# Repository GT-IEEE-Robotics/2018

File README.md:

# 2018
- 2018 Georgia Tech IEEE Hardware Team Repository
- Competition: 2018 Southeastcon Robotics Competition in Jacksonville, Florida
- Objective: to create an autonomous robot to navigate through various tasks in a minimal time frame

### Contents
- `Application`
    - Graphic User Interface robot controller
- `Competiton`
    - Final competition code and documentation
- `Distance Sensing`
    - Course detection and localization
- `Load Lifting`
    - Resources for lifting treasure weight
- `Miscellaneous`
    - Non competition relevant resouces
- `Motor Controller`
    - Motor control code and interface API
- `Navigation`
    - Course navigation theory and controller
- `Photodiode`
    - Start up infared signal generation and detection 
- `PRU`
    - Beaglebone black programmable real time units quadrature encoder reading
- [Rules](USF_IEEE_2018_SoutheastCon_HardwareRules_V3_2.pdf)

### To Do's
- [ ] List TODO's

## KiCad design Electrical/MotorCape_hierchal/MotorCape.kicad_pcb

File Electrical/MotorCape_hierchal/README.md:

# Arduino KiCad Library
Library of schematic components and footprints of common Arduino boards for KiCAD.

Currently included are:
- Arduino 101 Shield
- Arduino Due Shield
- Arduino Leonard Shied
- Arduino Mega 2560 Shield
- Arduino Micro Socket
- Arduino Uno Shield
- Arduino Zero Shield

Shield means the Arduino is designed to plug in from beneath your PCB; socket means it is designed to plug in from above.

## Library Setup
To add this library to your KiCad Project, do the following steps:
1. Copy the source files to your Project. Make sure that the Arduino.pretty folder structure is preserved.
2. In EeSchema (the schematic editor of KiCad) go to Preferences -> Component Libraries. Click the "Add" button next to "Component library files".
3. Navigate to your project folder, select "arduino.lib" and click "open".
4. You may wish to adjust the newly added arduino schematic library to be near the top of the load order using the "Up" and "Down" buttons, but this is optional and is only relevant if you have other libraries that use the same names for parts.
5. OK out and exit EeSchema. Open PcbNew (the PCB editor of KiCad) go to Preferences -> Footprint Libraries Manager.
6. Select the "Project Specific Libraries" tab and then click "Append Library".
7. In the new line of the table, set Library Path to "$(KIPRJMOD)\Arduino.pretty" and ensure Plugin Type is "KiCad". Options and Description can be left blank. You should set Nickname to something descriptive - like "Arduino" for example!
8. All done: you are now ready to use these schematic components and footprints!

## Comments, Requests, Bugs & Contributions
All are welcome. Please file an "Issue" in the Bug Tracker.

## License
This library is licensed under the GNU LGPL v2.1, which can be found in file LICENSE.txt.

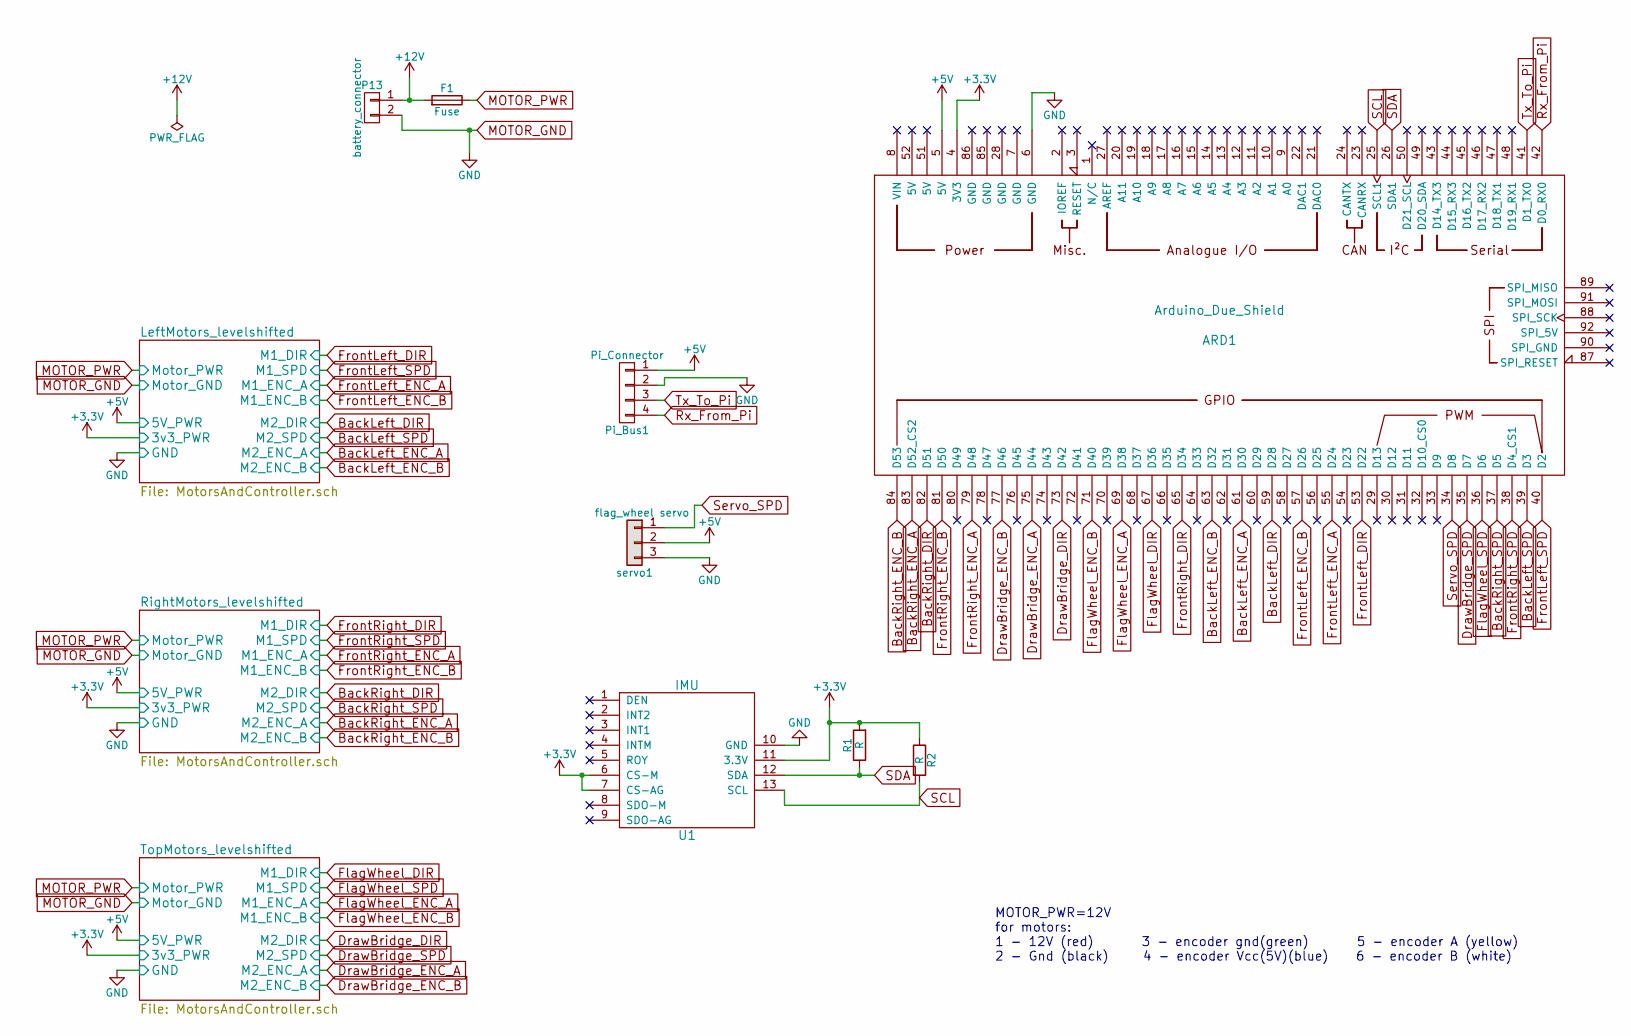
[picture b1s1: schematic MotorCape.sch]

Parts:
ARD1: Arduino_Due_Shield
F1: Fuse; Fuseholder_horizontal_inline_1_25x0_25_inch
P13: battery_connector; Molex_Sabre_43160-XX02_02x7.49mm_Vertical_BoardLock
Pi_Bus1: Pi_Connector; Pin_Header_Latched_1x04
R1, R2: R; R_Axial_DIN0204_L3.6mm_D1.6mm_P5.08mm_Horizontal
U1: IMU
servo1: flag_wheel servo; Pin_Header_Latched_1x03

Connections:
+3V3: ARD1.4 (3V3), R1.2, R2.1, U1.6 (CS-M), U1.7 (CS-AG), U1.11 (3.3V); also elsewhere on the board
+5V: ARD1.5 (5V), Pi_Bus1.1, servo1.2; also elsewhere on the board
+12V: F1.2, P13.1
BackLeft_DIR: ARD1.59 (D28); also elsewhere on the board
BackLeft_ENC_A: ARD1.61 (D30); also elsewhere on the board
BackLeft_ENC_B: ARD1.63 (D32); also elsewhere on the board
BackLeft_SPD: ARD1.39 (D3); also elsewhere on the board
BackRight_DIR: ARD1.82 (D51); also elsewhere on the board
BackRight_ENC_A: ARD1.83 (D52_CS2); also elsewhere on the board
BackRight_ENC_B: ARD1.84 (D53); also elsewhere on the board
BackRight_SPD: ARD1.37 (D5); also elsewhere on the board
DrawBridge_DIR: ARD1.73 (D42); also elsewhere on the board
DrawBridge_ENC_A: ARD1.75 (D44); also elsewhere on the board
DrawBridge_ENC_B: ARD1.77 (D46); also elsewhere on the board
DrawBridge_SPD: ARD1.35 (D7); also elsewhere on the board
FlagWheel_DIR: ARD1.67 (D36); also elsewhere on the board
FlagWheel_ENC_A: ARD1.69 (D38); also elsewhere on the board
FlagWheel_ENC_B: ARD1.71 (D40); also elsewhere on the board
FlagWheel_SPD: ARD1.36 (D6); also elsewhere on the board
FrontLeft_DIR: ARD1.53 (D22); also elsewhere on the board
FrontLeft_ENC_A: ARD1.55 (D24); also elsewhere on the board
FrontLeft_ENC_B: ARD1.57 (D26); also elsewhere on the board
FrontLeft_SPD: ARD1.40 (D2); also elsewhere on the board
FrontRight_DIR: ARD1.65 (D34); also elsewhere on the board
FrontRight_ENC_A: ARD1.79 (D48); also elsewhere on the board
FrontRight_ENC_B: ARD1.81 (D50); also elsewhere on the board
FrontRight_SPD: ARD1.38 (D4_CS1); also elsewhere on the board
MOTOR_GND: ARD1.6 (GND), P13.2, Pi_Bus1.2, U1.10 (GND), servo1.3; also elsewhere on the board
MOTOR_PWR: F1.1; also elsewhere on the board
Rx_From_Pi: ARD1.42 (D0_RX0), Pi_Bus1.4
SCL: ARD1.25 (SCL1), R2.2, U1.13 (SCL)
SDA: ARD1.26 (SDA1), R1.1, U1.12 (SDA)
Servo_SPD: ARD1.34 (D8), servo1.1
Tx_To_Pi: ARD1.41 (D1_TX0), Pi_Bus1.3

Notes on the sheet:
MOTOR_PWR=12V for motors: 1 - 12V (red) 3 - encoder gnd(green) 5 - encoder A (yellow) 2 - Gnd (black) 4 - encoder Vcc(5V)(blue) 6 - encoder B (white)

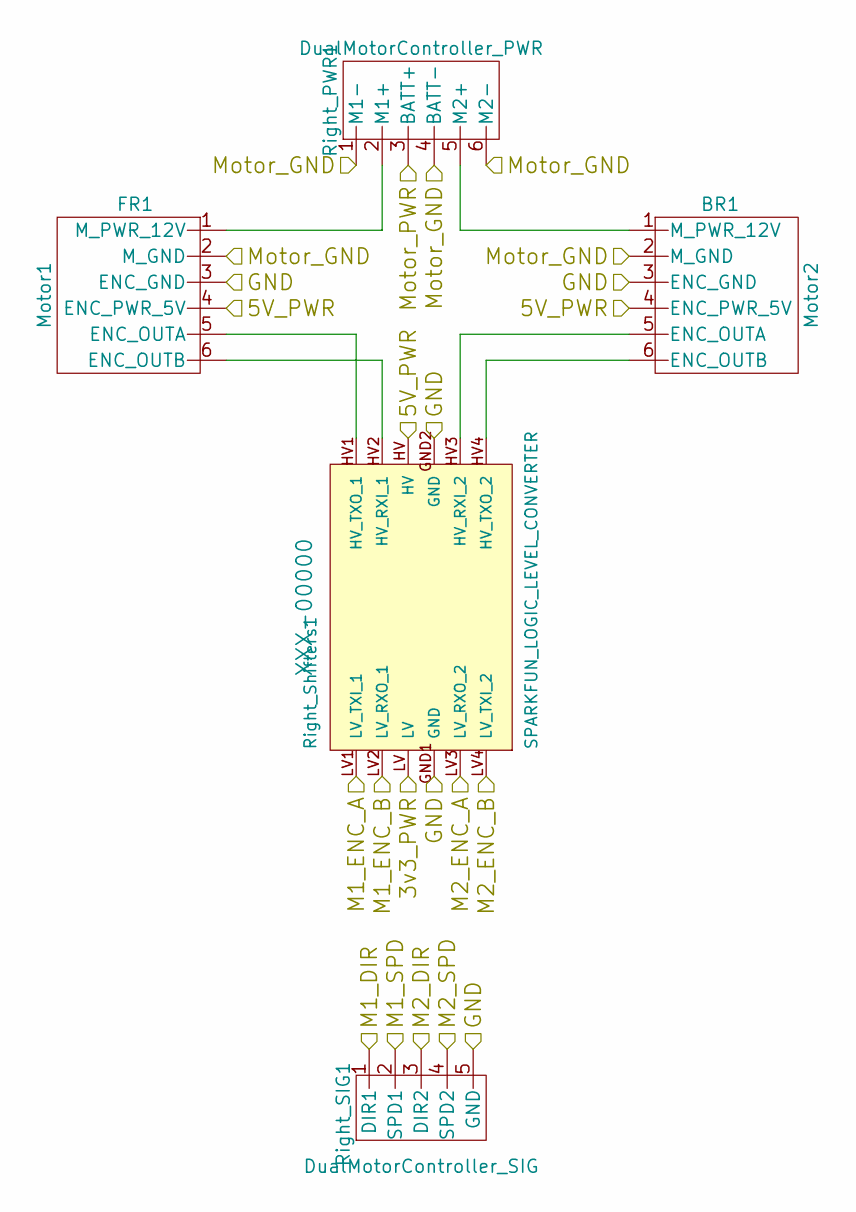
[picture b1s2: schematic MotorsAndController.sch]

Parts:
BL1: Motor2; Pin_Header_Latched_1x06
FL1: Motor1; Pin_Header_Latched_1x06
Left_PWR1: DualMotorController_PWR; PhoenixContact_MSTBA-G_06x5.08mm_Angled
Left_SIG1: DualMotorController_SIG; Pin_Header_Latched_1x05
Left_Shifters1: SPARKFUN_LOGIC_LEVEL_CONVERTER

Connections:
+3V3: Left_Shifters1.LV; also elsewhere on the board
+5V: BL1.4 (ENC_PWR_5V), FL1.4 (ENC_PWR_5V), Left_Shifters1.HV; also elsewhere on the board
BackLeft_DIR: Left_SIG1.3 (DIR2); also elsewhere on the board
BackLeft_ENC_A: Left_Shifters1.LV3 (LV_RXO_2); also elsewhere on the board
BackLeft_ENC_B: Left_Shifters1.LV4 (LV_TXI_2); also elsewhere on the board
BackLeft_SPD: Left_SIG1.4 (SPD2); also elsewhere on the board
FrontLeft_DIR: Left_SIG1.1 (DIR1); also elsewhere on the board
FrontLeft_ENC_A: Left_Shifters1.LV1 (LV_TXI_1); also elsewhere on the board
FrontLeft_ENC_B: Left_Shifters1.LV2 (LV_RXO_1); also elsewhere on the board
FrontLeft_SPD: Left_SIG1.2 (SPD1); also elsewhere on the board
MOTOR_GND: BL1.2 (M_GND), BL1.3 (ENC_GND), FL1.2 (M_GND), FL1.3 (ENC_GND), Left_PWR1.1 (M1-), Left_PWR1.4 (BATT-), Left_PWR1.6 (M2-), Left_SIG1.5 (GND), Left_Shifters1.GND1 (GND), Left_Shifters1.GND2 (GND); also elsewhere on the board
MOTOR_PWR: Left_PWR1.3 (BATT+); also elsewhere on the board
unnamed: BL1.1 (M_PWR_12V), Left_PWR1.5 (M2+)
unnamed: BL1.5 (ENC_OUTA), Left_Shifters1.HV3 (HV_RXI_2)
unnamed: BL1.6 (ENC_OUTB), Left_Shifters1.HV4 (HV_TXO_2)
unnamed: FL1.1 (M_PWR_12V), Left_PWR1.2 (M1+)
unnamed: FL1.5 (ENC_OUTA), Left_Shifters1.HV1 (HV_TXO_1)
unnamed: FL1.6 (ENC_OUTB), Left_Shifters1.HV2 (HV_RXI_1)

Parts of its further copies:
BR1: Motor2; Pin_Header_Latched_1x06
DrawBridge1: Motor2; Pin_Header_Latched_1x06
FR1: Motor1; Pin_Header_Latched_1x06
FlagWheel1: Motor1; Pin_Header_Latched_1x06
Right_PWR1: DualMotorController_PWR; PhoenixContact_MSTBA-G_06x5.08mm_Angled
Right_SIG1: DualMotorController_SIG; Pin_Header_Latched_1x05
Right_Shifters1: SPARKFUN_LOGIC_LEVEL_CONVERTER
Top_PWR1: DualMotorController_PWR; PhoenixContact_MSTBA-G_06x5.08mm_Angled
Top_SIG1: DualMotorController_SIG; Pin_Header_Latched_1x05
Top_Shifters1: SPARKFUN_LOGIC_LEVEL_CONVERTER

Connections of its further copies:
+3V3: Right_Shifters1.LV, Top_Shifters1.LV; also elsewhere on the board
+5V: BR1.4 (ENC_PWR_5V), DrawBridge1.4 (ENC_PWR_5V), FR1.4 (ENC_PWR_5V), FlagWheel1.4 (ENC_PWR_5V), Right_Shifters1.HV, Top_Shifters1.HV; also elsewhere on the board
BackRight_DIR: Right_SIG1.3 (DIR2); also elsewhere on the board
BackRight_ENC_A: Right_Shifters1.LV3 (LV_RXO_2); also elsewhere on the board
BackRight_ENC_B: Right_Shifters1.LV4 (LV_TXI_2); also elsewhere on the board
BackRight_SPD: Right_SIG1.4 (SPD2); also elsewhere on the board
DrawBridge_DIR: Top_SIG1.3 (DIR2); also elsewhere on the board
DrawBridge_ENC_A: Top_Shifters1.LV3 (LV_RXO_2); also elsewhere on the board
DrawBridge_ENC_B: Top_Shifters1.LV4 (LV_TXI_2); also elsewhere on the board
DrawBridge_SPD: Top_SIG1.4 (SPD2); also elsewhere on the board
FlagWheel_DIR: Top_SIG1.1 (DIR1); also elsewhere on the board
FlagWheel_ENC_A: Top_Shifters1.LV1 (LV_TXI_1); also elsewhere on the board
FlagWheel_ENC_B: Top_Shifters1.LV2 (LV_RXO_1); also elsewhere on the board
FlagWheel_SPD: Top_SIG1.2 (SPD1); also elsewhere on the board
FrontRight_DIR: Right_SIG1.1 (DIR1); also elsewhere on the board
FrontRight_ENC_A: Right_Shifters1.LV1 (LV_TXI_1); also elsewhere on the board
FrontRight_ENC_B: Right_Shifters1.LV2 (LV_RXO_1); also elsewhere on the board
FrontRight_SPD: Right_SIG1.2 (SPD1); also elsewhere on the board
MOTOR_GND: BR1.2 (M_GND), BR1.3 (ENC_GND), DrawBridge1.2 (M_GND), DrawBridge1.3 (ENC_GND), FR1.2 (M_GND), FR1.3 (ENC_GND), FlagWheel1.2 (M_GND), FlagWheel1.3 (ENC_GND), Right_PWR1.1 (M1-), Right_PWR1.4 (BATT-), Right_PWR1.6 (M2-), Right_SIG1.5 (GND), Right_Shifters1.GND1 (GND), Right_Shifters1.GND2 (GND), Top_PWR1.1 (M1-), Top_PWR1.4 (BATT-), Top_PWR1.6 (M2-), Top_SIG1.5 (GND), Top_Shifters1.GND1 (GND), Top_Shifters1.GND2 (GND); also elsewhere on the board
MOTOR_PWR: Right_PWR1.3 (BATT+), Top_PWR1.3 (BATT+); also elsewhere on the board
unnamed: BR1.1 (M_PWR_12V), Right_PWR1.5 (M2+)
unnamed: BR1.5 (ENC_OUTA), Right_Shifters1.HV3 (HV_RXI_2)
unnamed: BR1.6 (ENC_OUTB), Right_Shifters1.HV4 (HV_TXO_2)
unnamed: DrawBridge1.1 (M_PWR_12V), Top_PWR1.5 (M2+)
unnamed: DrawBridge1.5 (ENC_OUTA), Top_Shifters1.HV3 (HV_RXI_2)
unnamed: DrawBridge1.6 (ENC_OUTB), Top_Shifters1.HV4 (HV_TXO_2)
unnamed: FR1.1 (M_PWR_12V), Right_PWR1.2 (M1+)
unnamed: FR1.5 (ENC_OUTA), Right_Shifters1.HV1 (HV_TXO_1)
unnamed: FR1.6 (ENC_OUTB), Right_Shifters1.HV2 (HV_RXI_1)
unnamed: FlagWheel1.1 (M_PWR_12V), Top_PWR1.2 (M1+)
unnamed: FlagWheel1.5 (ENC_OUTA), Top_Shifters1.HV1 (HV_TXO_1)
unnamed: FlagWheel1.6 (ENC_OUTB), Top_Shifters1.HV2 (HV_RXI_1)

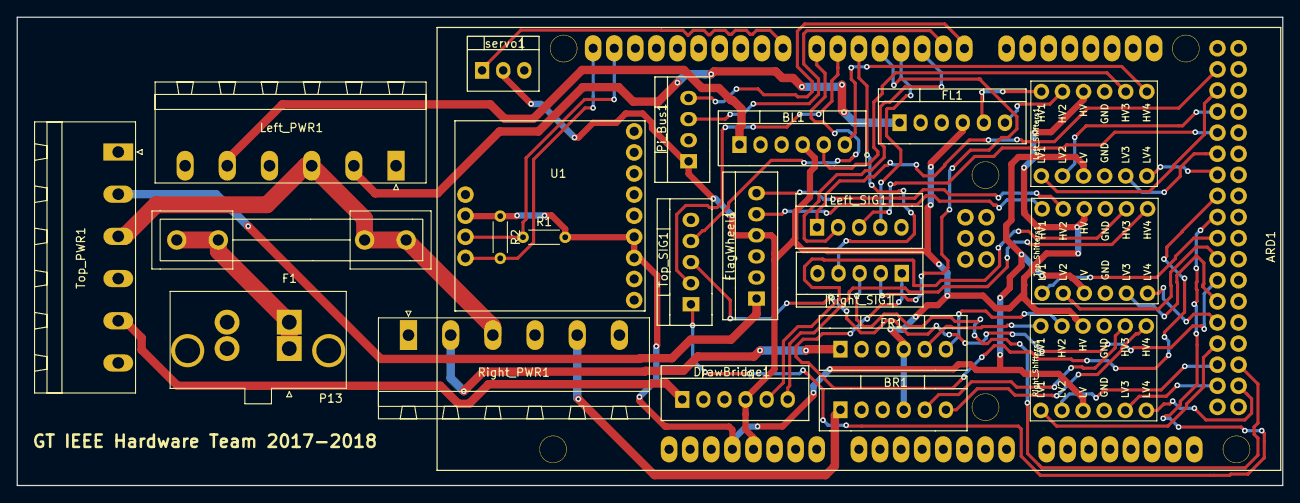
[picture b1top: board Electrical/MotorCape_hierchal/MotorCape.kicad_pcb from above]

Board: 2 copper layers, 152.4 x 56.4 mm, 23 parts (0 on the bottom side), 52 nets.

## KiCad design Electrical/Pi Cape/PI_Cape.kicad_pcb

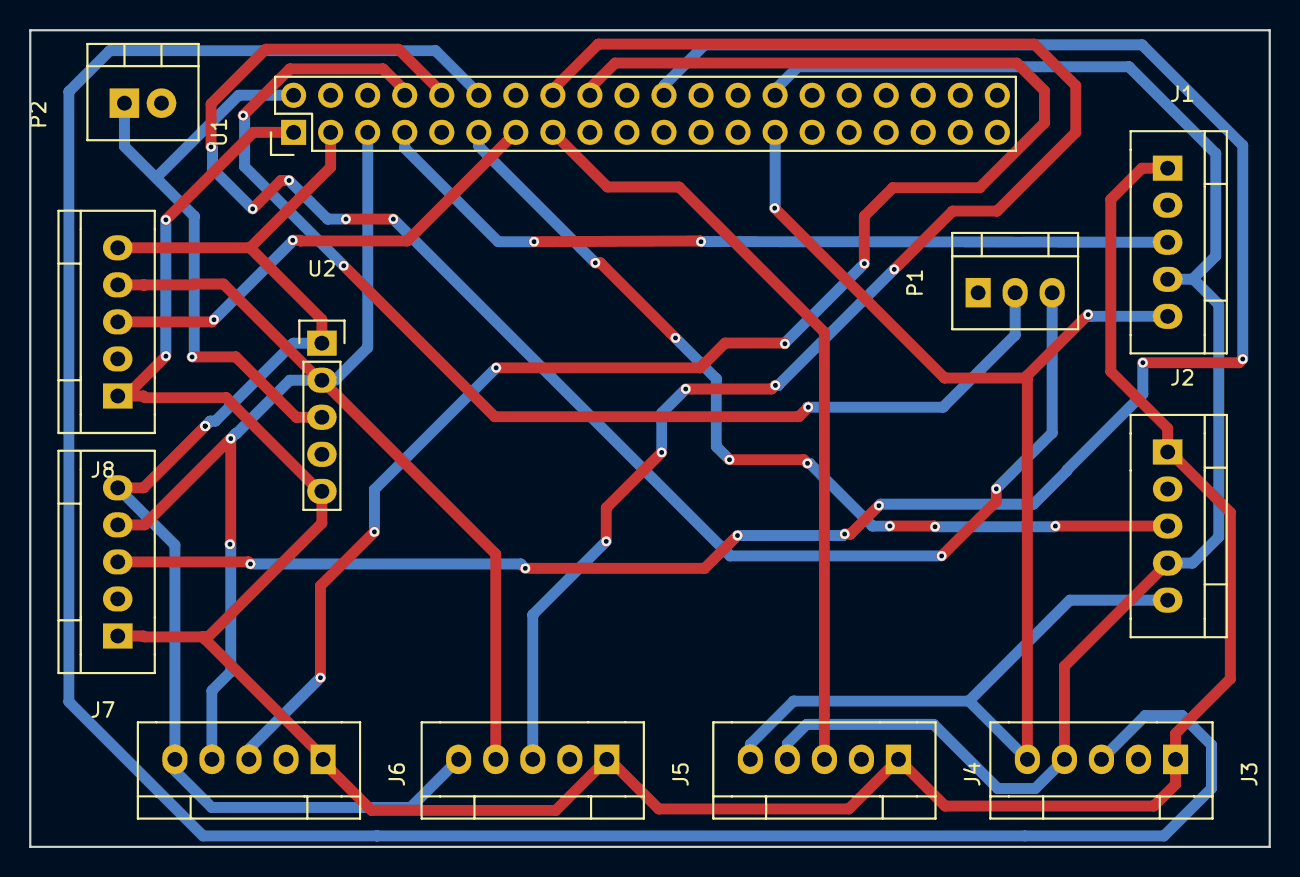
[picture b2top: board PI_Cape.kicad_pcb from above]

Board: 2 copper layers, 85.0 x 56.0 mm, 12 parts (0 on the bottom side), 17 nets.

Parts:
J1, J2, J3, J4, J5, J6, J7, J8: Dist_Sensor; Pin_Header_Latched_1x05
P1: Arduino_Interface; Pin_Header_Latched_1x03
P2: 5V_PWR_FROM_REGULATOR; Pin_Header_Latched_1x02
U1: Raspberry_Pi_2_3; Pin_Header_Straight_2x20
U2: 7-segment_LED; Pin_Header_Straight_1x05

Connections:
5V_PWR_IN: P2.1, U1.2, U2.3
GND: J1.2, J2.2, J3.2, J4.2, J5.2, J6.2, J7.2, J8.2, P1.1, P2.2, U1.6, U2.4
I2C0_SCL: J1.4, J2.4, J3.4, J4.4, U1.28
I2C0_SDA: J1.5, J2.5, J3.5, J4.5, U1.27
I2C1_SCL: J5.4, J6.4, J7.4, J8.4, U1.5, U2.2
I2C1_SDA: J5.5, J6.5, J7.5, J8.5, U1.3, U2.1
unnamed: P1.2, U1.8
unnamed: P1.3, U1.10
Vin: J1.1, J2.1, J3.1, J4.1, J5.1, J6.1, J7.1, J8.1, U1.1, U2.5
nEN_BL: J3.3, U1.12
nEN_BR: J4.3, U1.15
nEN_FL: J1.3, U1.7
nEN_FR: J2.3, U1.11
nEN_LB: J6.3, U1.18
nEN_LF: J5.3, U1.16
nEN_RB: J8.3, U1.13
nEN_RF: J7.3, U1.22

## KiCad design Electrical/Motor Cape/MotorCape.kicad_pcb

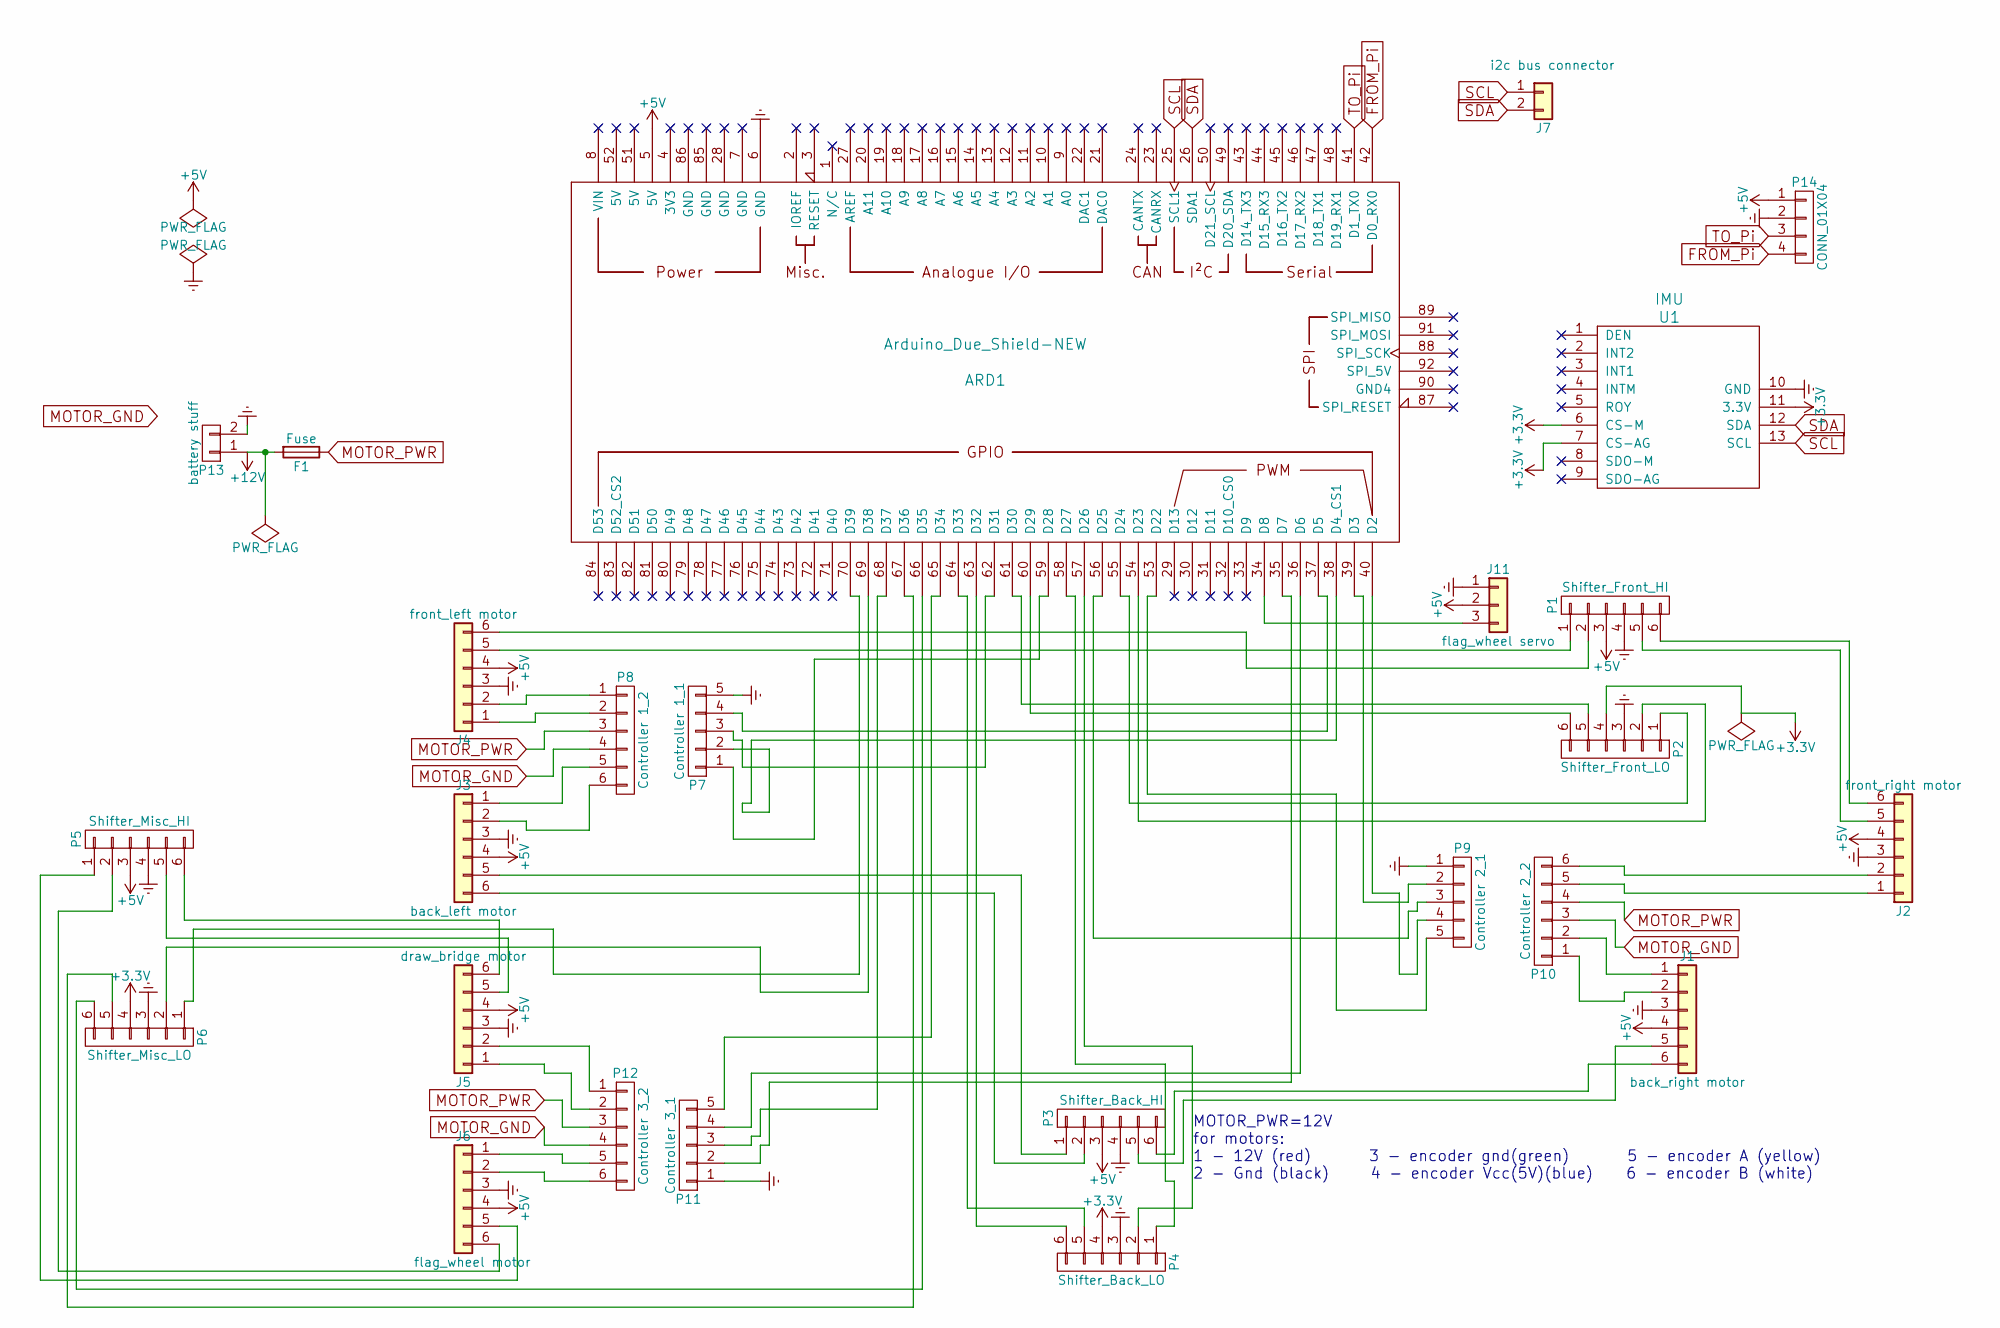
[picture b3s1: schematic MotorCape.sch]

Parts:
ARD1: Arduino_Due_Shield-NEW; Arduino_Due_Shield
F1: Fuse; Fuseholder5x20_horiz_open_inline_Type-I
J1: back_right motor; Pin_Header_Straight_1x06
J2: front_right motor; Pin_Header_Straight_1x06
J3: back_left motor; Pin_Header_Straight_1x06
J4: front_left motor; Pin_Header_Straight_1x06
J5: draw_bridge motor; Pin_Header_Straight_1x06
J6: flag_wheel motor; Pin_Header_Straight_1x06
J7: i2c bus connector; Pin_Header_Straight_1x02
J11: flag_wheel servo; Pin_Header_Straight_1x03
P1: Shifter_Front_HI; Pin_Header_Straight_1x06
P2: Shifter_Front_LO; Pin_Header_Straight_1x06
P3: Shifter_Back_HI; Pin_Header_Straight_1x06
P4: Shifter_Back_LO; Pin_Header_Straight_1x06
P5: Shifter_Misc_HI; Pin_Header_Straight_1x06
P6: Shifter_Misc_LO; Pin_Header_Straight_1x06
P7: Controller 1_1; Pin_Header_Straight_1x05
P8: Controller 1_2; TerminalBlock_Pheonix_MPT-2.54mm_6pol
P9: Controller 2_1; Pin_Header_Straight_1x05
P10: Controller 2_2; TerminalBlock_Pheonix_MPT-2.54mm_6pol
P11: Controller 3_1; Pin_Header_Straight_1x05
P12: Controller 3_2; TerminalBlock_Pheonix_MPT-2.54mm_6pol
P13: battery stuff; Pin_Header_Straight_1x02
P14: CONN_01X04; Pin_Header_Straight_1x04
U1: IMU

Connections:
+3V3: P2.4, P4.4, P6.4, U1.6 (CS-M), U1.7 (CS-AG), U1.11 (3.3V)
+5V: ARD1.5 (5V), J1.4, J2.4, J3.4, J4.4, J5.4, J6.4, J11.2, P1.3, P3.3, P5.3, P14.1
+12V: F1.2, P13.1
Earth: ARD1.6 (GND), J1.3, J2.3, J3.3, J4.3, J5.3, J6.3, J11.1, P1.4, P2.3, P3.4, P4.3, P5.4, P6.3, P7.5, P9.1, P11.1, P13.2, P14.2, U1.10 (GND)
FROM_Pi: ARD1.42 (D0_RX0), P14.4
MOTOR_GND: P8.4, P10.3, P12.4
MOTOR_PWR: F1.1, P8.3, P10.4, P12.3
unnamed: ARD1.34 (D8), J11.3
unnamed: ARD1.35 (D7), P11.2
unnamed: ARD1.36 (D6), P11.4
unnamed: ARD1.37 (D5), P7.4
unnamed: ARD1.38 (D4_CS1), P7.2
unnamed: ARD1.39 (D3), P9.2
unnamed: ARD1.40 (D2), P9.4
unnamed: ARD1.53 (D22), P9.5
unnamed: ARD1.54 (D23), P2.2
unnamed: ARD1.55 (D24), P2.1
unnamed: ARD1.56 (D25), P9.3
unnamed: ARD1.57 (D26), P4.2
unnamed: ARD1.58 (D27), P4.1
unnamed: ARD1.59 (D28), P7.1
unnamed: ARD1.60 (D29), P2.6
unnamed: ARD1.61 (D30), P2.5
unnamed: ARD1.62 (D31), P7.3
unnamed: ARD1.63 (D32), P4.6
unnamed: ARD1.64 (D33), P4.5
unnamed: ARD1.65 (D34), P11.5
unnamed: ARD1.66 (D35), P6.6
unnamed: ARD1.67 (D36), P6.5
unnamed: ARD1.68 (D37), P11.3
unnamed: ARD1.69 (D38), P6.2
unnamed: ARD1.70 (D39), P6.1
unnamed: J1.1, P10.2
unnamed: J1.2, P10.1
unnamed: J1.5, P3.5
unnamed: J1.6, P3.6
unnamed: J2.1, P10.5
unnamed: J2.2, P10.6
unnamed: J2.5, P1.5
unnamed: J2.6, P1.6
unnamed: J3.1, P8.5
unnamed: J3.2, P8.6
unnamed: J3.5, P3.1
unnamed: J3.6, P3.2
unnamed: J4.1, P8.2
unnamed: J4.2, P8.1
unnamed: J4.5, P1.1
unnamed: J4.6, P1.2
unnamed: J5.1, P12.2
unnamed: J5.2, P12.1
unnamed: J5.5, P5.5
unnamed: J5.6, P5.6
unnamed: J6.1, P12.5
unnamed: J6.2, P12.6
unnamed: J6.5, P5.1
unnamed: J6.6, P5.2
SCL: ARD1.25 (SCL1), J7.1, U1.13 (SCL)
SDA: ARD1.26 (SDA1), J7.2, U1.12 (SDA)
TO_Pi: ARD1.41 (D1_TX0), P14.3

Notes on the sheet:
MOTOR_PWR=12V for motors: 1 - 12V (red) 3 - encoder gnd(green) 5 - encoder A (yellow) 2 - Gnd (black) 4 - encoder Vcc(5V)(blue) 6 - encoder B (white)

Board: 2 copper layers, 25 parts (0 on the bottom side), 59 nets, no tracks yet.

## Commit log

2017-06-02 keyword: sexy
2017-06-02 fixing errors
2017-06-03 smokin
2017-06-07 try try again
2017-06-08 simple motor controller
2017-06-09 working time based code
2017-06-22 no idea
2017-07-08 old motor tests
2017-09-07 kicad tutorial
2017-09-28 new rules
2017-09-29 fixed it
2017-09-29 moved beaglebonecopypasta.cpp to app_note.cpp and added doxygen documentation & inital adaptations from mbed to linx. still need to change i2c class/function calls
2017-10-01 working motor test with uno
2017-10-26 Pulled piController from pi and pushed to remote github repo.
2017-10-27 Made basic controller library for robot.
2017-10-27 Convert tuple output to Serial String in a nice inside function
2017-10-27 Added move for programmers who don't want to deal with inside code
2017-10-29 Archives old files to avoid polluting namespace. Also, those files are kinda pointless now.
2017-10-31 Added test suite.
2017-10-31 Changed folders to make more logical files
2017-10-31 Turned everything into OOP and made program a lot more robust.
2017-10-31 Get rid of old files and general cleanup.
2017-11-02 added my old vl6180 time of flight distance sensor library and multiple qr code reader in case it's helpful to people
2017-11-03 Converted everything into a nice library with exceptions, unit tests and good ol' OOP concepts. May we never see shitty bash-like scripts again.
2017-11-03 Added proper references to each python module.
2017-11-03 Application
2017-11-03 Updating Application
2017-11-03 slight update
2017-11-06 clean up and organization
2017-11-06 updated application
2017-11-09 Add custom errors for better debugging.
2017-11-09 Adding file changes to avoid merge conflict
2017-11-09 Tangled source code from scratch. Not sure why this disappeared. Must investigate in order to prevent this from happening in the future. For now, must find a way for org-mode to tangle and create stu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
2017-11-10 Added instruction support to interactive GUI
2017-11-10 added motor cape files from KiCAD to repo
2017-11-10 Updating MotorController Code
2017-11-16 Worked on wiring motor cape connections.
2017-11-17 Changes made during meeting
2017-11-17 Adding other files correctly
2017-11-17 Adding remaining files
2018-01-26 updated electrical connections. need to finish connectors on schematic.
2018-01-26 updated labels
2018-01-26 added level shifters and due and pi and labels
2018-01-27 fixed drc errors, added serial comm between pi & due, now just need to choose power connector & fuse
2018-01-31 updated to supposed final version of rules
2018-02-16 added pi ICD
2018-02-16 arduino umm due footprint hahahah youre adding the um haha
2018-02-16 Removes KalmanFilter.py and replaces with IIR filter
2018-02-16 Finished Filter. Will update docs soon.
2018-02-16 Cleaning up stragglers
2018-02-16 trying to add xcel for bom
2018-02-17 Moving changes from Sensor.py to controller.org and adding documentation.
2018-02-17 Added logging & warnings to Compass.py. Moved Compass.py from direction folder.
2018-02-17 Added better documentation to Instruction class and moved it to picontroller folder.
2018-02-17 Added better documentation to Coordinate class and moved it to picontroller folder.
2018-02-18 Fixed a few org-mode issues with tangling.
2018-02-18 Checkpoint for module import issues.
2018-02-18 Removed picontroller to its own repo
2018-02-18 Removing picontroller files from main repo
2018-02-23 added ICD for pi and arduino
2018-02-23 added column for used connections/signals in IMU
2018-02-23 Added tutorial testing code for IMU
2018-02-23 worked more on motor cape
2018-02-23 modified links on connection diagram
2018-02-23 organized and cleaned up connections document. just need 3 more connectors for the arduino shield
2018-02-24 pi and arduino connector choice completed except battery connector
2018-02-24 finished all connectors. now to do schematic and footprint association
2018-03-01 starting pi cape schematic
2018-03-01 updated Pi and Arduino external connection. Finished base Pi schematic
2018-03-02 added gud stuff
2018-03-08 moved imu from pi to arduino on excel sheets
2018-03-16 not sure if i updated arduino connections recently but it said it changed
2018-03-16 pushing aldriges changes to arduino board
2018-03-16 finished updates on pi schematic, working on footprints next
2018-03-20 finished footprints on Pi cape. onto layouts
2018-03-20 added onboard robot folders & transfered files
2018-03-20 added Jon's IMU code to OnTheArduino and shuffled folders
2018-03-21 updated pi cape to have 7-seg and spaced components in layout
2018-03-21 added preliminary comments on mecanum wheel movement vectors
2018-03-22 copies of both github & arduino are there. i'll merge them when i get home
2018-03-29 added distance sensor code
2018-03-30 added newest rules 3.3-1 stuff
2018-03-30 added actual 'final' rules. realized i added only the change log
2018-03-30 Added basic implementation of movement PID on heading
2018-04-04 initialized shell for relative heading for indoors
2018-04-05 updated sensor code
2018-04-05 moved into init functions (dist sensors)
2018-04-05 pushing global modification
2018-04-05 added code
2018-04-05 mark added python magic
2018-04-05 asasdf stuff about string things
2018-04-05 marc's name is spelled marc :+1:
2018-04-05 fixed samarthya thing class bus 1
2018-04-06 changed one line or two
2018-04-06 put stuff back
2018-04-06 messed with more stuff
2018-04-06 committed one line
2018-04-06 added dual bus manual test
2018-04-06 sensor stuff
2018-04-06 stuff
2018-04-06 stuff:
2018-04-06 more stuff
2018-04-06 sensors pls
2018-04-06 sensors
2018-04-06 importing one sensor lib at a time
2018-04-06 heck yeah
2018-04-06 finally
2018-04-06 new commit
2018-04-06 added initial seven seg stuff
2018-04-07 turned motor cape hiercichal, updated connector footprints to have latch, updated bettery connector, and did initial spacing on layout
2018-04-07 trying to lay-out things. lots of via's, this could be a bit messy
2018-04-08 pushing changes while routing. still not done yet
2018-04-08 did some PID tuning
2018-04-09 pushing latest motor controller layout changes
2018-04-09 did some testing with i2c
2018-04-09 distance sensor library modification
2018-04-09 added distance sensor lib mods
2018-04-10 finished the hierarchicalalala motor cape board
2018-04-10 starting to work on dist sensor stuff
2018-04-10 fixed ctype error
2018-04-10 c lib modifications to add bus number
2018-04-10 added default param for bus_num in i2c_read
2018-04-10 fixed build errors for i2c_read
2018-04-10 added bus_number to a lot of the c lib functions
2018-04-10 fixed py indentation error
2018-04-10 debugging
2018-04-10 implemented bus_num into c lib's sensor structs
2018-04-10 start debugging
2018-04-10 debug
2018-04-12 added bunch of stuff
2018-04-12 arduino imu updates
2018-04-13 trying to fix pid
2018-04-14 added imu heading correction code
2018-04-14 starting particle filter code
2018-04-14 added particle filter code
2018-04-16 fixed pi repos
2018-04-17 added hardcode
2018-04-17 removed extra python code, added functions to make arduino code shorter
2018-04-19 added files after the wlan0 broke
2018-04-19 encoder stuff
2018-04-19 modified encoder test
2018-04-19 fixed encoder.ino
2018-04-19 made a bombass imu class
2018-04-19 cleaning up gyro theta class
2018-04-19 fixed the imu class
2018-04-19 kicad stuff
2018-04-19 fixed pid code
2018-04-19 gyro stuff
2018-04-20 added file to gen sensor readings
2018-04-20 added sensor reading files
2018-04-20 setting up full system test folder on arduino
2018-04-20 successfully tested all encoders on motor controller board
2018-04-20 added new sensor readings
2018-04-21 pushing stuff for arduino
2018-04-21 added lirc files
2018-04-21 Velocity PID wheel drive initial upload
2018-04-21 added stuff
2018-04-21 updated pin locations
2018-04-21 added servo
2018-04-21 flag motor test
2018-04-21 implemented communication and commands
